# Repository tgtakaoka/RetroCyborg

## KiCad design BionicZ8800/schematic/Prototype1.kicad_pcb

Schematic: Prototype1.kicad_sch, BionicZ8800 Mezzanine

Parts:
C1: 0.1u; C_Disc_D3.4mm_W2.1mm_P2.50mm
J1: BionicConnector; DIP-48_W7.62mm
U1: Z88C00; DIP-48_W15.24mm
U2: 74HCT126; DIP-14_W7.62mm

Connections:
/P10: J1.2 (P10), U1.1 (AD0)
/P11: J1.3 (P11), U1.2 (AD1)
/P12: J1.4 (P12), U1.3 (AD2)
/P13: J1.5 (P13), U1.4 (AD3)
/P14: J1.6 (P14), U1.5 (AD4)
/P15: J1.7 (P15), U1.6 (AD5)
/P16: J1.8 (P16), U1.7 (AD6)
/P17: J1.9 (P17), U1.8 (AD7)
/P20: J1.47 (P20), U1.48 (A8)
/P21: J1.46 (P21), U1.47 (A9)
/P22: J1.45 (P22), U1.46 (A10)
/P23: J1.44 (P23), U1.45 (A11)
/P24: J1.43 (P24), U1.44 (A12)
/P25: J1.42 (P25), U1.43 (A13)
/P26: J1.41 (P26), U1.42 (A14)
/P27: J1.40 (P27), U1.41 (A15)
/P40: J1.38 (P40), U1.38 (~AS)
/P41: J1.37 (P41), U1.31 (R/~W)
/P42: J1.36 (P42), U1.19 (P32), U1.23 (P21/~IRQ1)
/P43: J1.35 (P43), U1.20 (P33), U1.21 (P23/~IRQ0)
/P44: J1.34 (P44), U1.24 (TxD/P31)
/P45: J1.33 (P45), U1.25 (RxD/P30)
/P46: J1.32 (P46), U2.2 (1A)
/P47: J1.31 (P47), U1.37 (~DS)
/P50: J1.20 (P50), U1.26 (P26/~IRQ2)
/P52: J1.22 (P52), U1.40 (~WAIT/P34)
/P53: J1.23 (P53), U2.5 (2A)
/P55: J1.28 (P55), U1.39 (~DM/P35)
GND: C1.2, J1.1 (GND), J1.48 (GND), U1.34 (GND), U2.7 (GND), U2.9 (3A), U2.10 (3OE), U2.12 (4A), U2.13 (4OE)
unnamed: U1.13 (XTAL1), U2.3 (1Y)
unnamed: U1.30 (~RESET), U2.6 (2Y)
VCC: C1.1, J1.24 (VCC), J1.25 (VCC), U1.11 (VCC), U2.1 (1OE), U2.4 (2OE), U2.14 (VCC)

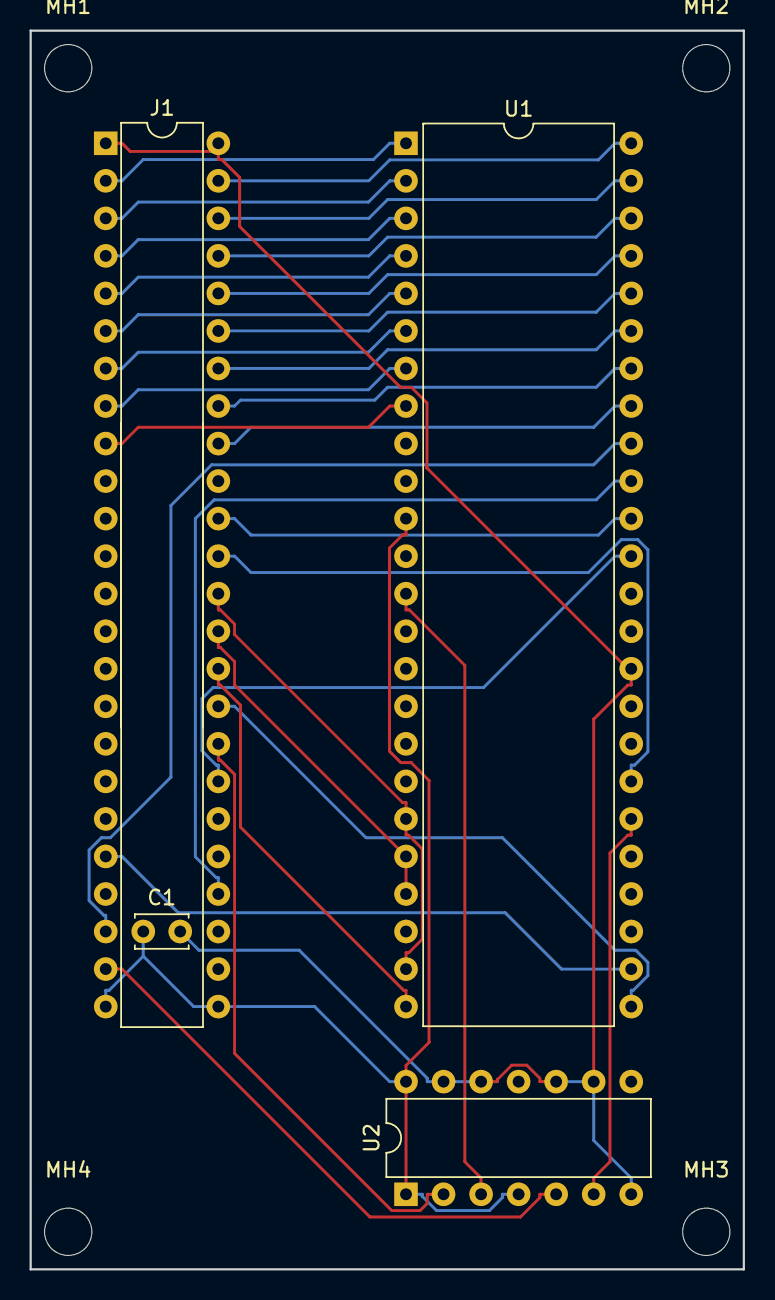
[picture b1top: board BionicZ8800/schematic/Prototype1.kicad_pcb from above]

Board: 2 copper layers, 48.3 x 83.8 mm, 8 parts (0 on the bottom side), 32 nets.

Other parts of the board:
MH1, MH2, MH3, MH4: MountingHole_3.2mm_M3

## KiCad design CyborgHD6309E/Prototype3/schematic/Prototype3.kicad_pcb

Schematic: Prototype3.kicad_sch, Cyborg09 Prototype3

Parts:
C1, C2, C5, C6, C7: 0.1u; C_0603_1608Metric
C3, C4, C8, C9: 22p; C_0402_1005Metric
D1: USR_LED; LED_D3.0mm
J1: Conn_USB_Serial; PinSocket_1x06_P2.54mm_Vertical
J2, J4: Conn_AVR_ISP; PinSocket_1x06_P2.54mm_Vertical
J3: Conn_Micro_SD; PinSocket_1x07_P2.54mm_Vertical
R1, R3, R4: 10k; R_0603_1608Metric
R2: 560; R_0603_1608Metric
SW1: USR_SW; Push_E-Switch_KS01Q01
U1: ATmega1284P-PU; DIP-40_W15.24mm_Socket
U2: HM628128DLP-5; DIP-32_W15.24mm_Socket
U3: HD63C09E; DIP-40_W15.24mm_Socket
U4: ATmega328P-PU; DIP-28_W7.62mm_Socket
Y1, Y2: 20MHz; Crystal_SMD_SeikoEpson_FA238-4Pin_3.2x2.5mm

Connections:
/A0: U1.3 (PB2), U2.12 (A0), U3.8 (A0)
/A1: U1.4 (PB3), U2.11 (A1), U3.9 (A1)
/A2: J4.4 (MISO), U2.10 (A2), U3.10 (A2), U4.18 (PB4)
/A3: J4.5 (MOSI), U2.9 (A3), U3.11 (A3), U4.17 (PB3)
/A4: U2.8 (A4), U3.12 (A4), U4.16 (PB2)
/A5: U2.7 (A5), U3.13 (A5), U4.2 (PD0)
/A6: U2.6 (A6), U3.14 (A6), U4.15 (PB1)
/A7: J4.3 (SCK), U2.5 (A7), U3.15 (A7), U4.19 (PB5)
/A8: U2.27 (A8), U3.16 (A8), U4.14 (PB0)
/A9: U2.26 (A9), U3.17 (A9), U4.3 (PD1)
/A10: U2.23 (A10), U3.18 (A10), U4.4 (PD2)
/A11: U2.25 (A11), U3.19 (A11), U4.5 (PD3)
/A12: U2.4 (A12), U3.20 (A12), U4.6 (PD4)
/A13: U2.28 (A13), U3.21 (A13), U4.11 (PD5)
/A14: U2.3 (A14), U3.22 (A14), U4.12 (PD6)
/A15: U2.31 (A15), U3.23 (A15), U4.13 (PD7)
/AVMA: U1.26 (PC4), U3.36 (AVMA)
/BA: U1.27 (PC5), U3.6 (BA)
/BS: U1.29 (PC7), U3.5 (BS)
/BUSY: U1.25 (PC3), U3.33 (BUSY)
/D0: U1.40 (PA0), U2.13 (Q0), U3.31 (D0)
/D1: U1.39 (PA1), U2.14 (Q1), U3.30 (D1)
/D2: U1.38 (PA2), U2.15 (Q2), U3.29 (D2)
/D3: U1.37 (PA3), U2.17 (Q3), U3.28 (D3)
/D4: U1.36 (PA4), U2.18 (Q4), U3.27 (D4)
/D5: U1.35 (PA5), U2.19 (Q5), U3.26 (D5)
/D6: U1.34 (PA6), U2.20 (Q6), U3.25 (D6)
/D7: U1.33 (PA7), U2.21 (Q7), U3.24 (D7)
/DBG_RX: J1.3 (TXD), U1.14 (RXD0/PD0)
/DBG_TX: J1.2 (RXD), U1.15 (TXD0/PD1)
/E_CLK: U2.30 (CS2), U3.34 (E), U4.27 (PC4)
/LIC: U1.28 (PC6), U3.38 (LIC)
/Q_CLK: U3.35 (Q), U4.28 (PC5)
/RD_WR: U1.24 (PC2), U2.29 (WR), U3.32 (R/~W)
/SD_DI: J2.5 (MOSI), J3.3 (DI), U1.6 (PB5/MOSI)
/SD_DO: J2.4 (MISO), J3.5 (DO), U1.7 (PB6/MISO)
/SD_SCK: J2.3 (SCK), J3.4 (SCK), U1.8 (PB7/SCK)
/USR_LED: D1.2 (A), U1.18 (PD4)
/~ACK: U1.20 (PD6), U4.25 (PC2)
/~DBG_RST: C2.2, J2.1 (~RESET), R1.1, U1.9 (~RESET)
/~HALT: U1.23 (PC1), U3.40 (~HALT)
/~INT: U1.17 (PD3), U4.26 (PC3)
/~IRQ: U1.2 (PB1), U3.3 (~IRQ)
/~NMI: U1.1 (PB0), U3.2 (~NMI)
/~RAM_E: U1.19 (PD5), U2.22 (CS1)
/~RESET: U1.22 (PC0), U3.37 (~RESET)
/~SD_CS: J3.2 (~CS), U1.5 (PB4/~SS)
/~STEP: U1.21 (PD7), U4.24 (PC1)
/~USR_SW: SW1.1, U1.16 (PD2)
GND: C1.2, C3.2, C4.1, C5.2, C6.2, C7.2, C8.2, C9.1, J1.5 (~CTS), J1.6 (GND), J2.6 (GND), J3.7 (GND), J4.6 (GND), R2.1, SW1.2, U1.11 (GND), U1.31 (GND), U2.2 (A16), U2.16 (GND), U2.24 (OE), U3.1 (VSS), U3.39 (TSC), U4.8 (GND), U4.22 (GND)
unnamed: C2.1, J1.1 (~DTR)
unnamed: C3.1, U1.13 (XTAL1), Y1.1
unnamed: C4.2, U1.12 (XTAL2), Y1.2
unnamed: C8.1, U4.9 (XTAL1), Y2.1
unnamed: C9.2, U4.10 (XTAL2), Y2.2
unnamed: D1.1 (K), R2.2
unnamed: J4.1 (~RESET), R4.1, U4.1 (~RESET)
unnamed: R3.1, U3.4 (~FIRQ)
VCC: C1.1, C5.1, C6.1, C7.1, J1.4 (5V0), J2.2 (VCC), J3.1 (VCC), J4.2 (VCC), R1.2, R3.2, R4.2, U1.10 (VCC), U1.30 (AVCC), U2.32 (VCC), U3.7 (VCC), U4.7 (VCC), U4.20 (AVCC)

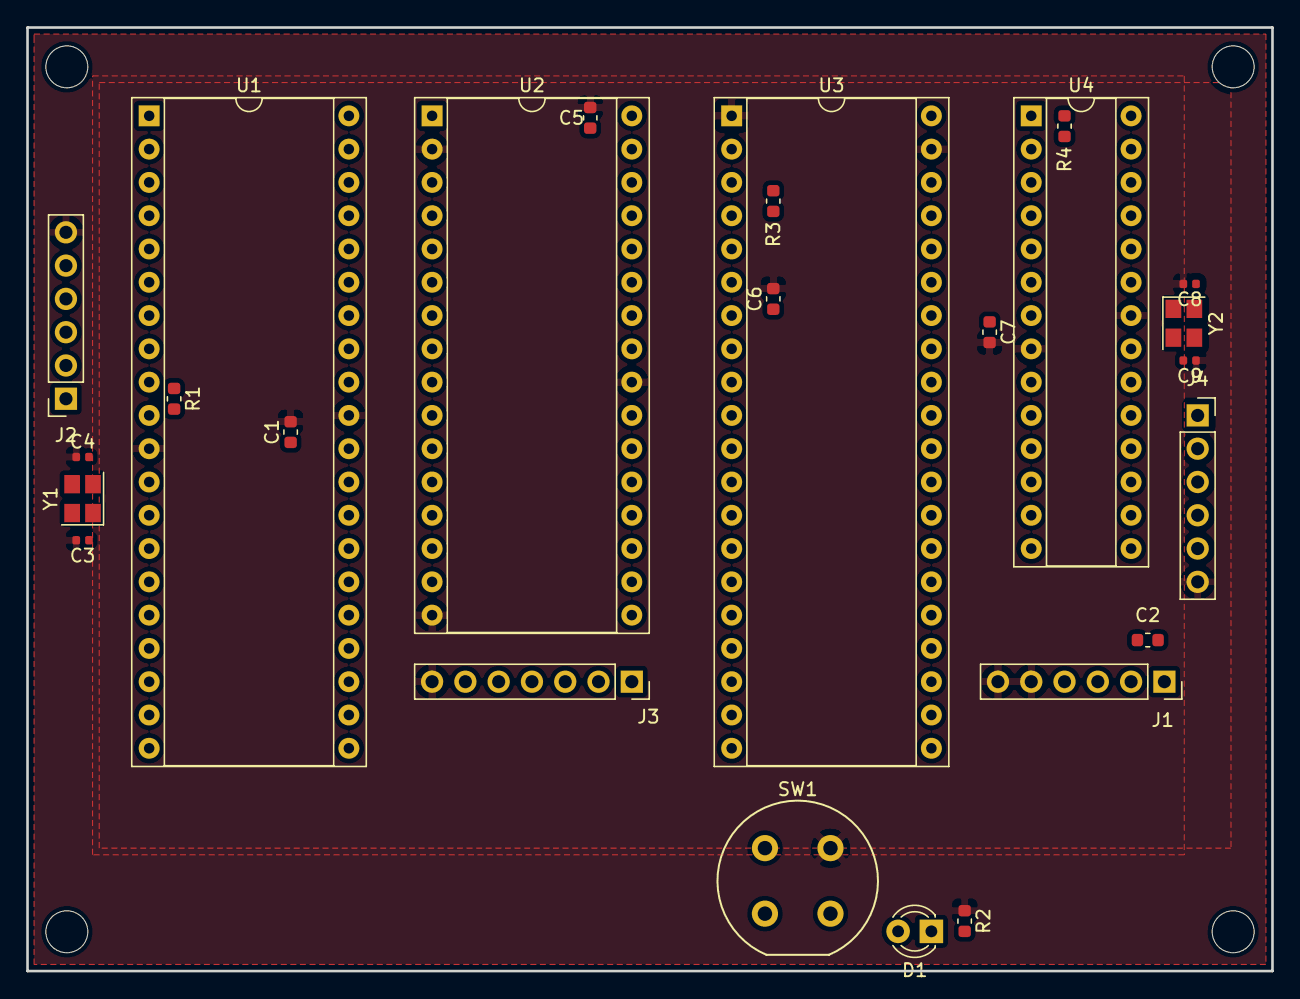
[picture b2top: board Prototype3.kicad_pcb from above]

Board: 2 copper layers, 95.0 x 72.0 mm, 29 parts (0 on the bottom side), 59 nets, no tracks yet.

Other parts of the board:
MH1, MH2, MH3, MH4: MountingHole_3.2mm_M3

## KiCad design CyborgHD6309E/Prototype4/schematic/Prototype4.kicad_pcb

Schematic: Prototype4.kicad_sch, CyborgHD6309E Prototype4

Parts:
B1: Micro_SD; uSD_CARD
B2: USB_Serial; GY232V2
C1, C2, C3, C4, C5, C6, C7: 0.1u; C_Disc_D3.4mm_W2.1mm_P2.50mm
J1: Conn_AVR_UPDI; PinSocket_1x03_P2.54mm_Vertical
R2, R3: 10k; R_Axial_DIN0204_L3.6mm_D1.6mm_P5.08mm_Horizontal
R6: 560; R_Axial_DIN0204_L3.6mm_D1.6mm_P5.08mm_Horizontal
SW1: TSD1265; SW_PUSH-LED-12mm
U1: ATmega4809-P; DIP-40_W15.24mm
U2: HM628128DLP-5; DIP-32_W15.24mm_Socket
U3: HD63C09E; DIP-40_W15.24mm_Socket
U4: ATtiny412-SS; DIP-8_W7.62mm
U5: CD74HCT30; DIP-14_W7.62mm
U6: CD74HCT688; DIP-20_W7.62mm

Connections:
/A0: U1.7 (PC4), U2.26 (A9), U3.8 (A0)
/A1: U1.8 (PC5), U2.25 (A11), U3.9 (A1)
/A2: U2.23 (A10), U3.10 (A2)
/A3: U2.3 (A14), U3.11 (A3), U6.17 (A7)
/A4: U2.4 (A12), U3.12 (A4), U6.15 (A6)
/A5: U2.5 (A7), U3.13 (A5), U6.13 (A5)
/A6: U2.6 (A6), U3.14 (A6), U6.11 (A4)
/A7: U2.7 (A5), U3.15 (A7), U6.8 (A3)
/A8: U2.8 (A4), U3.16 (A8), U5.12
/A9: U2.9 (A3), U3.17 (A9), U5.11
/A10: U2.10 (A2), U3.18 (A10), U5.1
/A11: U2.11 (A1), U3.19 (A11), U5.2
/A12: U2.12 (A0), U3.20 (A12), U5.3
/A13: U2.27 (A8), U3.21 (A13), U5.6
/A14: U2.28 (A13), U3.22 (A14), U5.5
/A15: U2.31 (A15), U3.23 (A15), U5.4
/AVMA: U1.12 (PD3), U3.36 (AVMA)
/BA: U1.14 (PD5), U3.6 (BA)
/BS: U1.13 (PD4), U3.5 (BS)
/BUSY: U1.16 (PD7), U3.33 (BUSY)
/D0: U1.33 (PA0), U2.21 (Q7), U3.31 (D0)
/D1: U1.34 (PA1), U2.20 (Q6), U3.30 (D1)
/D2: U1.35 (PA2), U2.19 (Q5), U3.29 (D2)
/D3: U1.36 (PA3), U2.18 (Q4), U3.28 (D3)
/D4: U1.37 (PA4), U2.17 (Q3), U3.27 (D4)
/D5: U1.38 (PA5), U2.13 (Q0), U3.26 (D5)
/D6: U1.39 (PA6), U2.14 (Q1), U3.25 (D6)
/D7: U1.40 (PA7), U2.15 (Q2), U3.24 (D7)
/DBG_RX: B2.4 (TXD), U1.1 (PC0/TXD)
/DBG_TX: B2.5 (RXD), U1.2 (PC1/RXD)
/E_CLK: U2.30 (CS2), U3.34 (E), U4.3 (PA7)
/LIC: U1.10 (PD1), U3.38 (LIC)
/Q_CLK: U3.35 (Q), U4.4 (PA1)
/RD_WR: U1.11 (PD2), U2.29 (WR), U3.32 (R/~W)
/SD_DI: B1.3 (DI), U1.19 (MOSI/PE0)
/SD_DO: B1.5 (DO), U1.20 (MISO/PE1)
/SD_SCK: B1.4 (SCK), U1.21 (SCK/PE2)
/USR_LED: R6.2, U1.27 (PF4)
/~ACK: U1.3 (PC2/SDA), U4.6 (UPDI/PA0)
/~DBG_RESET: C7.2, R3.1, U1.29 (~RESET/PF6)
/~HALT: U1.15 (PD6), U3.40 (~HALT)
/~INT: U1.25 (PF2), U4.7 (PA3)
/~IRQ: U1.23 (PF0), U3.3 (~IRQ)
/~NMI: U1.24 (PF1), U3.2 (~NMI)
/~RAM_E: U1.4 (PC3/SCL), U2.22 (CS1)
/~RESET: U1.9 (PD0), U3.37 (~RESET)
/~SD_CS: B1.2 (~CS), U1.22 (SS/PE3)
/~STEP: U1.26 (PF3), U4.5 (PA2)
/~USR_SW: SW1.2, U1.28 (PF5)
GND: B1.7 (GND), B2.1 (GND), B2.2 (~CTS), C1.2, C2.2, C3.2, C4.2, C5.2, C6.2, J1.2 (GND), SW1.1, SW1.3 (K), U1.6 (GND), U1.18 (GND), U1.32 (GND), U2.2 (A16), U2.16 (GND), U2.24 (OE), U3.1 (VSS), U3.39 (TSC), U4.8 (GND), U5.7 (GND), U6.2 (A0), U6.3 (B0), U6.4 (A1), U6.5 (B1), U6.6 (A2), U6.7 (B2), U6.10 (GND), U6.14 (B5), U6.16 (B6), U6.18 (B7)
unnamed: B2.6 (~DTR), C7.1
unnamed: J1.1 (UPDI), U1.30 (UPDI)
unnamed: R2.2, U3.4 (~FIRQ)
unnamed: R6.1, SW1.4 (A)
unnamed: U4.2 (PA6), U6.19 (~Y)
unnamed: U5.8, U6.1 (~E)
VCC: B1.1 (VCC), B2.3 (5V0), C1.1, C2.1, C3.1, C4.1, C5.1, C6.1, J1.3 (VCC), R2.1, R3.2, U1.5 (VCC), U1.17 (AVCC), U1.31 (VCC), U2.32 (VCC), U3.7 (VCC), U4.1 (VCC), U5.14 (VCC), U6.9 (B3), U6.12 (B4), U6.20 (VCC)

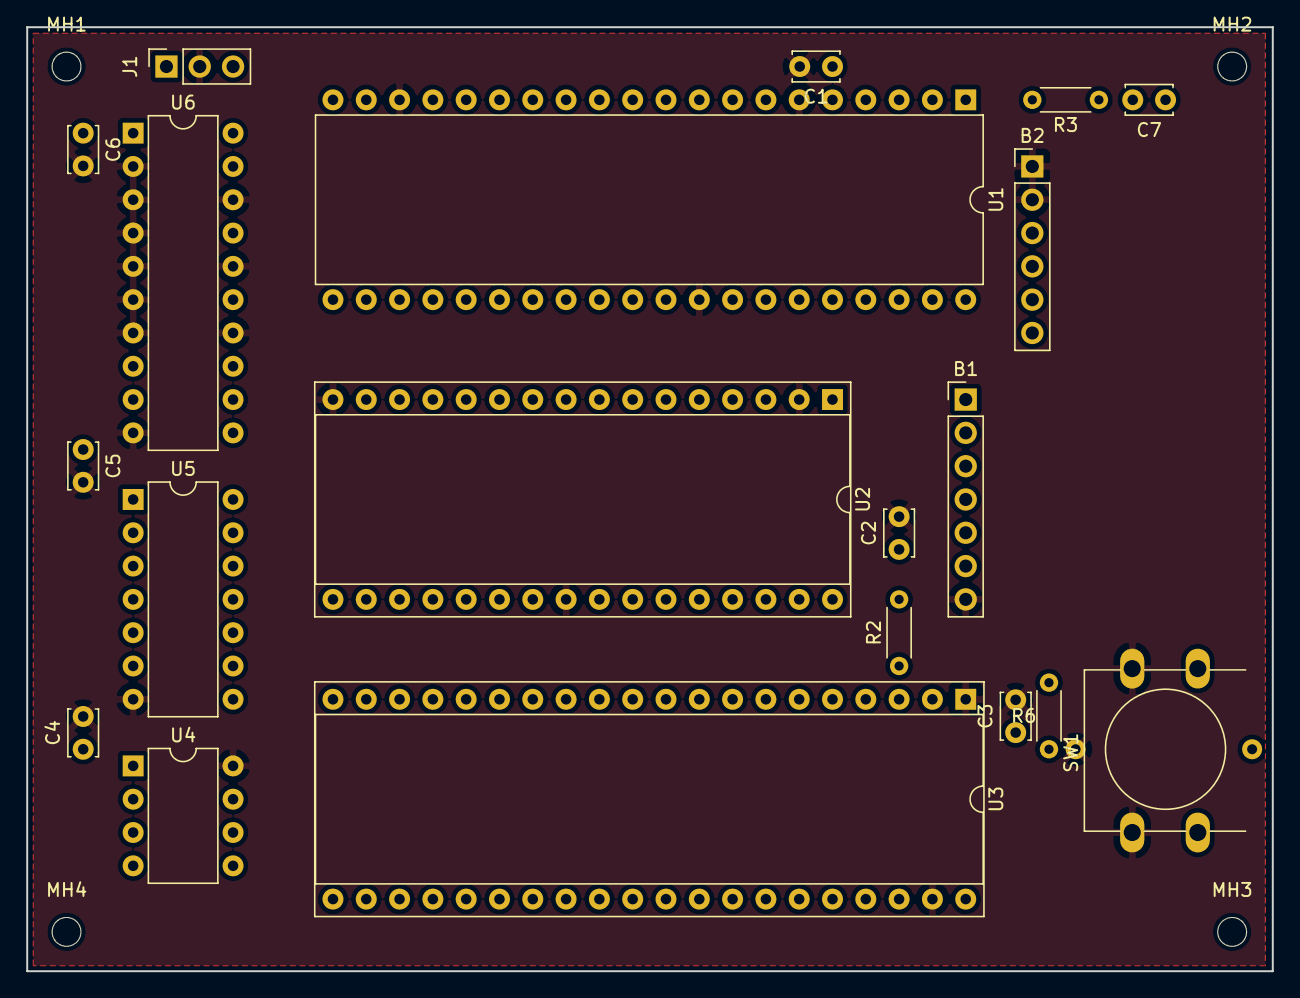
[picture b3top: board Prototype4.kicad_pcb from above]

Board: 2 copper layers, 95.0 x 72.0 mm, 24 parts (0 on the bottom side), 57 nets, no tracks yet.

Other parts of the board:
MH1, MH2, MH3, MH4: MountingHole_2.2mm_M2

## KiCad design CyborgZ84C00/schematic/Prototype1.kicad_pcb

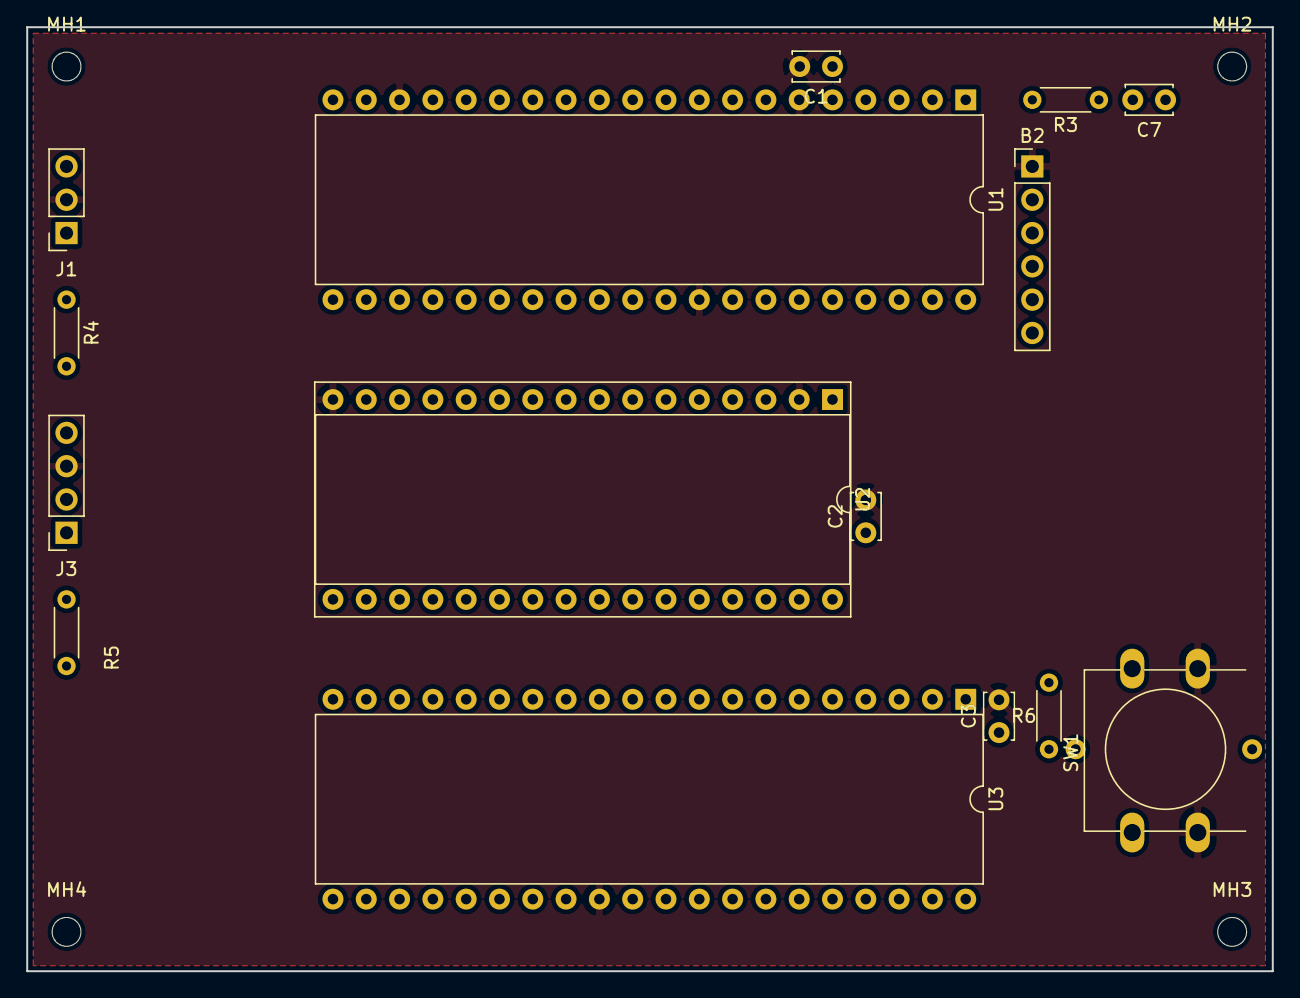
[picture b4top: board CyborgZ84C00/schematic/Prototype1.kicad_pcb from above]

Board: 2 copper layers, 95.0 x 72.0 mm, 19 parts (0 on the bottom side), 50 nets, no tracks yet.

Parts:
B2: USB_Serial; GY232V2
C1, C2, C3, C7: 0.1u; C_Disc_D3.4mm_W2.1mm_P2.50mm
J1: Conn_AVR_UPDI; PinSocket_1x03_P2.54mm_Vertical
J3: Conn_I2C_Master; PinSocket_1x04_P2.54mm_Vertical
MH1, MH2, MH3, MH4: MountingHole_2.2mm_M2
R3: 10k; R_Axial_DIN0204_L3.6mm_D1.6mm_P5.08mm_Horizontal
R4, R5: 4k7; R_Axial_DIN0204_L3.6mm_D1.6mm_P5.08mm_Horizontal
R6: 560; R_Axial_DIN0204_L3.6mm_D1.6mm_P5.08mm_Horizontal
SW1: TSD1265; SW_PUSH-LED-12mm
U1: ATmega4809-P; DIP-40_W15.24mm
U2: HM628128DLP-5; DIP-32_W15.24mm_Socket
U3: Z84C00; DIP-40_W15.24mm

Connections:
/A0: U1.25, U2.26, U3.30
/A1: U1.26, U2.25, U3.31
/A2: U2.23, U3.32
/A3: U2.3, U3.33
/A4: U2.4, U3.34
/A5: U2.5, U3.35
/A6: U2.6, U3.36
/A7: U2.7, U3.37
/A8: U2.8, U3.38
/A9: U2.9, U3.39
/A10: U2.10, U3.40
/A11: U2.11, U3.1
/A12: U2.12, U3.2
/A13: U2.27, U3.3
/A14: U2.28, U3.4
/A15: U2.31, U3.5
/CLK: U1.28, U3.6
/D0: U1.9, U2.21, U3.14
/D1: U1.10, U2.20, U3.15
/D2: U1.11, U2.19, U3.12
/D3: U1.12, U2.18, U3.8
/D4: U1.13, U2.17, U3.7
/D5: U1.14, U2.13, U3.9
/D6: U1.15, U2.14, U3.10
/D7: U1.16, U2.15, U3.13
/DBG_RX: B2.4, U1.1
/DBG_TX: B2.5, U1.2
/SCL: J3.4, R4.2
/SDA: J3.1, R5.2
/~BUSACK: U1.40, U3.23
/~BUSREQ: U1.39, U3.25
/~DBG_RESET: C7.2, R3.1, U1.29
/~DBG_RTS: B2.2, U1.8
/~INT: U1.23, U3.16
/~IORQ: U1.33, U3.20
/~M1: U1.35, U3.27
/~MREQ: U1.34, U3.19
/~NMI: U1.24, U3.17
/~RAM_E: U1.3, U2.22
/~RD: U1.37, U2.24, U3.21
/~RESET: U1.27, U3.26
/~USR_LED: R6.2, U1.7
/~USR_SW: SW1.1, U1.4
/~WAIT: U1.36, U3.24
/~WR: U1.38, U2.29, U3.22
GND: B2.1, C1.2, C2.2, C3.2, J1.2, J3.3, SW1.2, U1.6, U1.18, U1.32, U2.2, U2.16, U3.29
unnamed: B2.6, C7.1
unnamed: J1.1, U1.30
unnamed: R6.1, SW1.3
VCC: B2.3, C1.1, C2.1, C3.1, J1.3, J3.2, R3.2, R4.1, R5.1, SW1.4, U1.5, U1.17, U1.31, U2.30, U2.32, U3.11

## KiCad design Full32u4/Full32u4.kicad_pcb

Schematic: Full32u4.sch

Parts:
C1: 0.1u; C_0603_1608Metric
C2: 1u; C_0603_1608Metric
D1: 30V1A; D_DO-201AD_P3.81mm_Vertical_AnodeUp
J1: AE-USB-MICRO; AE-USB-MICRO-B-D
J2, J3: Conn_01x16; PinHeader_1x16_P2.54mm_Vertical
R1, R2: 22; R_Axial_DIN0207_L6.3mm_D2.5mm_P2.54mm_Vertical
R3: 10k; R_Axial_DIN0204_L3.6mm_D1.6mm_P1.90mm_Vertical
U1: ATmega32U4-AU; AE-QFP44RP8-DIP
Y1: 16MHz; Resonator-3Pin_W6.0mm_H3.0mm

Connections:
GND: C1.2, C2.2, J1.5 (GND), J2.10, J3.13, U1.5 (UGND), U1.15 (GND), U1.23 (GND), U1.35 (GND), U1.43 (GND), Y1.2
unnamed: C1.1, U1.42 (AREF)
unnamed: C2.1, U1.6 (UCAP)
unnamed: J1.2 (D-), R1.2
unnamed: J1.3 (D+), R2.2
unnamed: R1.1, U1.3 (D-)
unnamed: R2.1, U1.4 (D+)
unnamed: U1.16 (XTAL2), Y1.1
unnamed: U1.17 (XTAL1), Y1.3
PB0: J2.4, U1.8 (PB0)
PB1: J2.12, U1.9 (PB1)
PB2: J2.5, U1.10 (PB2)
PB3: J2.13, U1.11 (PB3)
PB4: J3.7, U1.28 (PB4)
PB5: J3.10, U1.29 (PB5)
PB6: J3.6, U1.30 (PB6)
PB7: J2.6, U1.12 (PB7)
PC6: J3.9, U1.31 (PC6)
PC7: J3.5, U1.32 (PC7)
PD0: J2.16, U1.18 (PD0)
PD1: J3.16, U1.19 (PD1)
PD2: J2.15, U1.20 (PD2)
PD3: J3.15, U1.21 (PD3)
PD4: J3.12, U1.25 (PD4)
PD5: J2.14, U1.22 (PD5)
PD6: J3.14, U1.26 (PD6)
PD7: J3.11, U1.27 (PD7)
PE2: J3.8, U1.33 (~HWB~/PE2)
PE6: J2.8, U1.1 (PE6)
PF0: J2.3, U1.41 (PF0)
PF1: J3.2, U1.40 (PF1)
PF4: J2.2, U1.39 (PF4)
PF5: J3.3, U1.38 (PF5)
PF6: J2.1, U1.37 (PF6)
PF7: J3.4, U1.36 (PF7)
RESET: J2.7, R3.2, U1.13 (~RESET)
VBUS: D1.2 (A), J1.1 (VBUS), J2.11, U1.2 (UVCC), U1.7 (VBUS)
VCC: D1.1 (K), J3.1, R3.1, U1.14 (VCC), U1.24 (AVCC), U1.34 (VCC), U1.44 (AVCC)

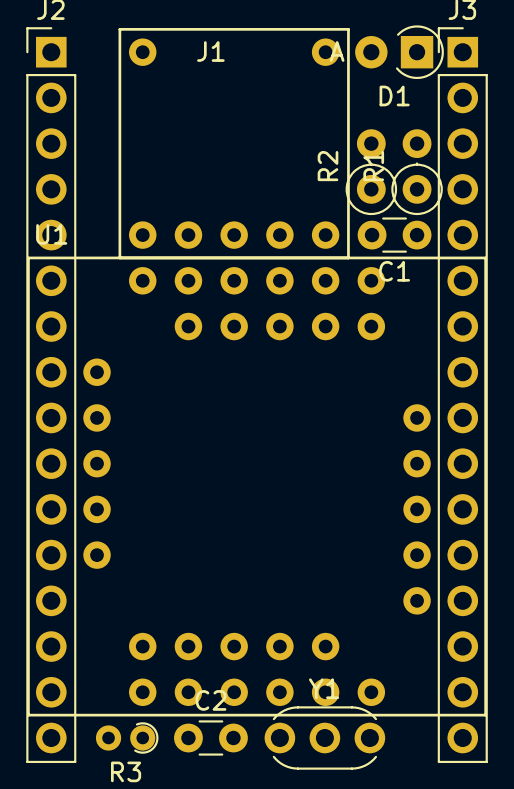
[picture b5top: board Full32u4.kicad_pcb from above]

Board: 2 copper layers, 11 parts (0 on the bottom side), 38 nets, no tracks yet.
